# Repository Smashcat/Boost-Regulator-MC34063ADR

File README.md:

# Boost-Regulator-MC34063ADR
Boost Regulator MC34063ADR test board

This is a test board to evaluate the MC3406 boost regulator.

Includes all production files.

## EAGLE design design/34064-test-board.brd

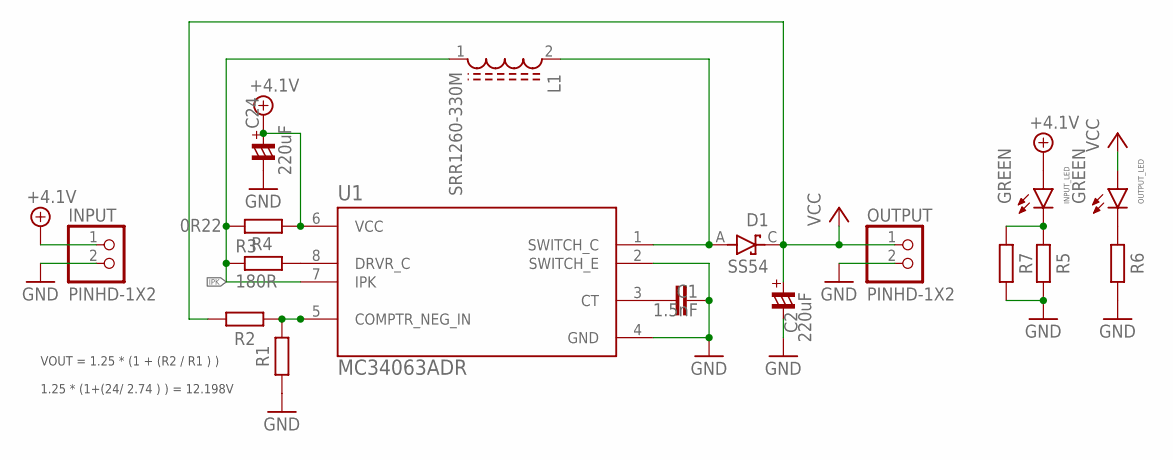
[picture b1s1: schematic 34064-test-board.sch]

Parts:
C1: 1.5nF; C0603
C2, C24: 220uF; RC-MASTER-SMD_C7343-43
D1: SS54; DIOM5336X265N
INPUT: PINHD-1X2; 1X02
INPUT_LED: GREEN; CHIPLED_0603
L1: SRR1260-330M; INDP125125X600N
OUTPUT: PINHD-1X2; 1X02
OUTPUT_LED: GREEN; CHIPLED_0603
R1: 2K2; R0402
R2: 20K; R0402
R3: 180R; R0603
R4: 0R22; R0805
R5, R6, R7: 2K74; R0402
U1: MC34063ADR; SOIC127P599X175-8N

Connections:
+4.1V: C24.+, INPUT.1, INPUT_LED.A, R4.2, U1.6 (VCC)
GND: C1.2, C2.-, C24.-, INPUT.2, OUTPUT.2, R1.2, R5.1, R6.1, R7.1, U1.2 (SWITCH_E), U1.4 (GND)
IPK: L1.1, R3.1, R4.1, U1.7 (IPK)
unnamed: R1.1, R2.2, U1.5 (COMPTR_NEG_IN)
unnamed: INPUT_LED.C, R5.2, R7.2
unnamed: D1.A, L1.2, U1.1 (SWITCH_C)
unnamed: C1.1, U1.3 (CT)
unnamed: OUTPUT_LED.C, R6.2
unnamed: R3.2, U1.8 (DRVR_C)
VCC: C2.+, D1.C (K), OUTPUT.1, OUTPUT_LED.A, R2.1

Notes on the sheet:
VOUT = 1.25 * (1 + (R2 / R1 ) ) 1.25 * (1+(24/ 2.74 ) ) = 12.198V

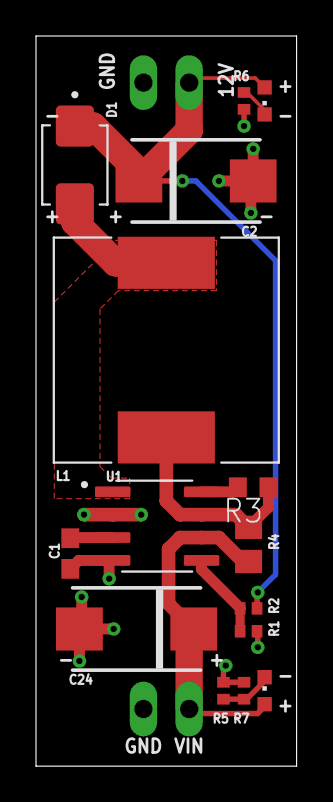
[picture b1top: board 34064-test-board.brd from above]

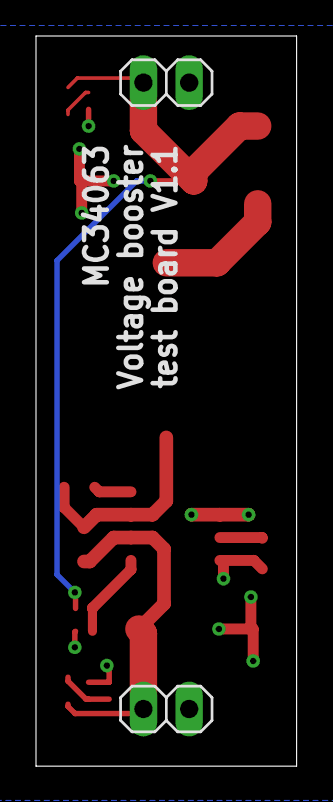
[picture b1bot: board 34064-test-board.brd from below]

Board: 2 copper layers, 14.5 x 40.6 mm, 17 parts (2 on the bottom side), 10 nets.
